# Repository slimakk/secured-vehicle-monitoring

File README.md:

# SECURED VEHICLE MONITORING USING OBDII AND LPWAN NETWORKS

This repository contains hardware design files and source code for bachelor thesis at FEEC BUT, which was sucessfully defended in 2023. The main goal behind the creation of this thesis was to create a device that would be capable of reporting important engine parameters to an external server for further processing.

[Link to a full thesis](https://www.vut.cz/studenti/zav-prace?zp_id=151037)
---------------------------------------------------------------------------
## Hardware specs
* MCU -- STM32 L431
* LPWAN module -- Quectel BG77, supports NB-IoT, LTE Cat M, GPS
* Power -- Synchronous Step-Down Converter by Texas Instruments
* Vehicle comms -- CAN Bus, K-Line, KWP2000
## Software
* OBD II support -- only mode 02
* Data transmission -- UDP, TCP, MQTT

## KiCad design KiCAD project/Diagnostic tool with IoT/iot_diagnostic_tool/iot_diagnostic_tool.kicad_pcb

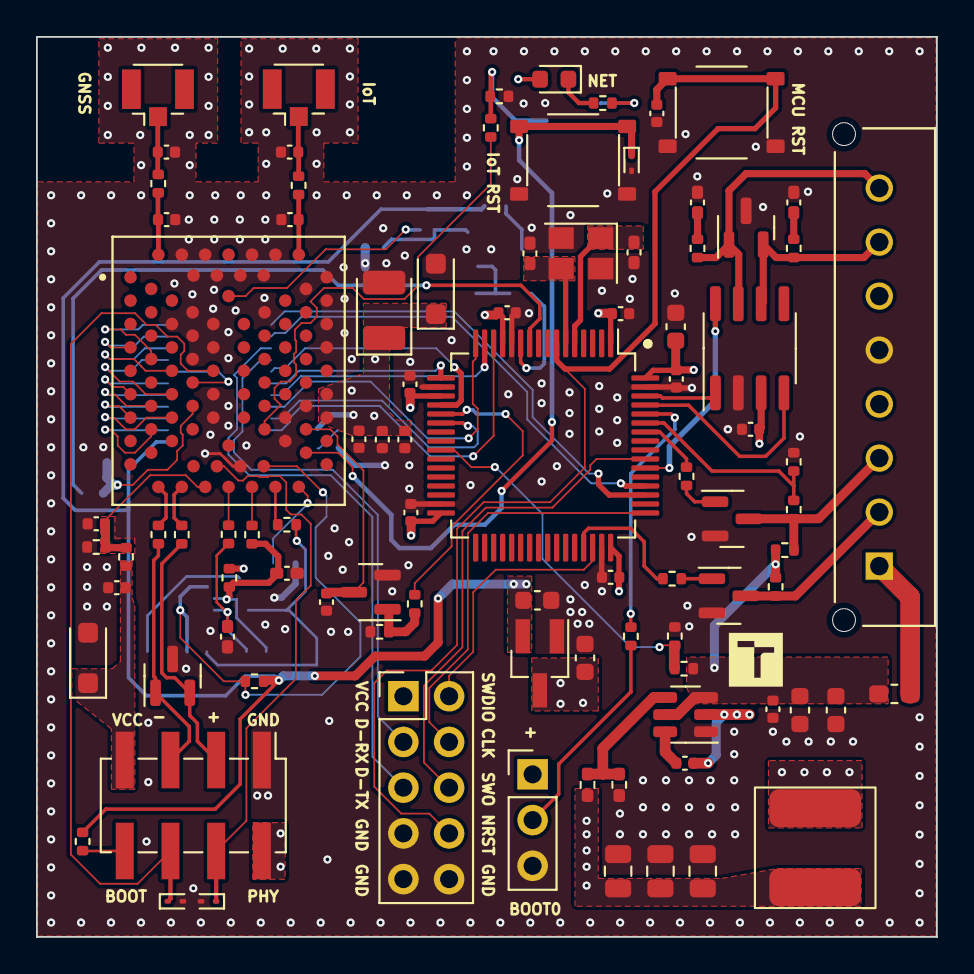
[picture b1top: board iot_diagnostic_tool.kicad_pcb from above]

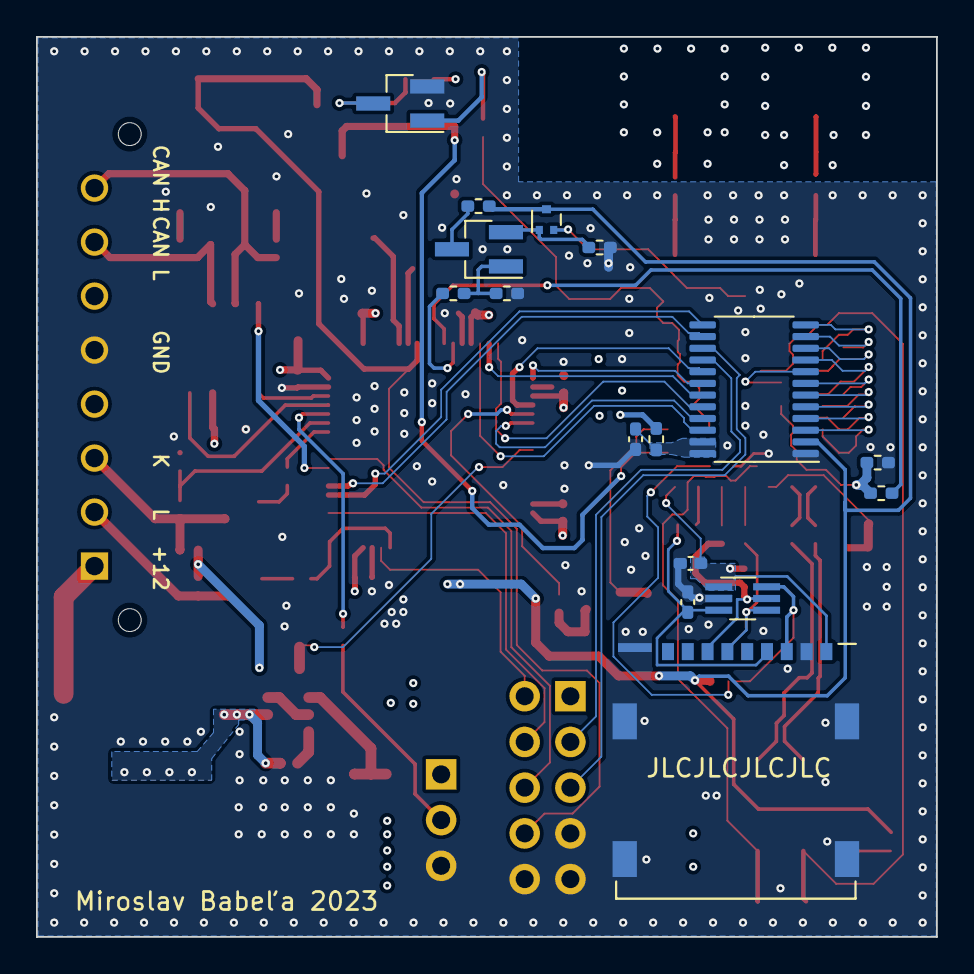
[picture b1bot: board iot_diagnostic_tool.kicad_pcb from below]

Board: 4 copper layers, 50.0 x 50.0 mm, 108 parts (16 on the bottom side), 88 nets.

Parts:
AE1: IoT_ANT; U.FL_Hirose_U.FL-R-SMT-1_Vertical
AE2: GNSS_ANT; U.FL_Hirose_U.FL-R-SMT-1_Vertical
C1: 4u7; C_0603_1608Metric
C2, C3, C4, C5, C6, C7, C8, C11, C14, C18, C23, C36: 100n; C_0402_1005Metric
C9, C10: 8p; C_0402_1005Metric_Pad0.74x0.62mm_HandSolder
C12, C13: 10u; C_0603_1608Metric
C15, C16, C17: 22u; C_0805_2012Metric
C19, C20: 560p; C_0402_1005Metric_Pad0.74x0.62mm_HandSolder
C21: 10p; C_0402_1005Metric
C22: 33p; C_0402_1005Metric
C24: 100u; CP_EIA-3528-21_Kemet-B
C25, C37: 10n; C_0402_1005Metric
C27, C32: 100n; C_0402_1005Metric_Pad0.74x0.62mm_HandSolder
C28, C29: 1u; C_0603_1608Metric
C33, C34, C35: 33p; C_0402_1005Metric_Pad0.74x0.62mm_HandSolder
C38, C39, C40, C41: NM; C_0402_1005Metric
D1: PESD2CAN; SOT-23
D2: LED; D_0603_1608Metric
D5: PESD5V0L5UY; SOT-363_SC-70-6_Handsoldering
D6, D11: TPSMF4L5.0A; D_SOD-123F
D7: PESD5V0X1BT,215; SOT-23
D8, D9, D10: ESD9L3.3; D_SOD-923
F1: 2A; Fuse_0603_1608Metric_Pad1.05x0.95mm_HandSolder
J2: USB; PinHeader_2x04_P2.54mm_Vertical_SMD
J3: 693023010811
J5: Debug; PinHeader_2x05_P2.54mm_Vertical
J6: BOOT; PinHeader_1x03_P2.54mm_Vertical
J7: OBD; MOLEX_436500827
L1: 3u3; VLS6045AF
Q1, Q2, Q4: BC817; SOT-23
Q3, Q5: BC817; SOT-23_Handsoldering
Q6: RUM001L02T2CL; SOT-723
R1, R34, R37: 10k; R_0402_1005Metric
R2: 33k2; R_0402_1005Metric_Pad0.72x0.64mm_HandSolder
R3, R40, R41, R44, R45: 10k; R_0402_1005Metric_Pad0.72x0.64mm_HandSolder
R4, R5: 100R; R_0402_1005Metric
R6, R8, R17: 2k2; R_0402_1005Metric
R7, R9: 510R; R_0402_1005Metric
R10, R12: 100k; R_0402_1005Metric
R11, R13: 27k; R_0402_1005Metric
R14, R18: 4k7; R_0402_1005Metric
R15, R19: 47k; R_0402_1005Metric
R16: 200k; R_0402_1005Metric_Pad0.72x0.64mm_HandSolder
R28, R29, R30, R35, R36, R38, R39: 0R; R_0402_1005Metric
R31: 51k; R_0402_1005Metric
R32: 15k; R_0402_1005Metric
R33: 20k; R_0402_1005Metric
R42, R43: 100k; R_0402_1005Metric_Pad0.72x0.64mm_HandSolder
SW1: RST; XKB_TS_1187A
SW3: IoT_RST; XKB_TS_1187A
U1: STM32L431RCTx; LQFP-64_10x10mm_P0.5mm
U2: TPS562201; SOT-23-6
U3: SN65HVD231; SOIC-8_3.9x4.9mm_P1.27mm
U4: BG77LA-64-SGNS; MODULE_BG77LA-64-SGNS
U6: AP2120N-1.8; SOT-23_Handsoldering
U8: NVT2010; TSSOP-24_4.4x7.8mm_P0.65mm
Y1: 16 MHz; Crystal_SMD_3225-4Pin_3.2x2.5mm

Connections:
+1V8: C29.1, Q6.3 (D), R31.1, R37.1, R40.1, U6.2 (VO), U8.2 (VREFA)
+3V3: C1.1, C2.1, C3.1, C4.1, C5.1, C6.1, C7.1, C15.1, C16.1, C17.1, C18.1, C21.1, C22.1, C23.1, C24.1, C28.1, D2.2 (A), D11.1 (K), J2.2, J5.1, J6.1, L1.2, R2.1, R16.1, U1.1 (VBAT), U1.13 (VDDA), U1.19 (VDD), U1.32 (VDD), U1.48 (VDD), U1.64 (VDD), U3.3 (VCC), U4.19 (VBAT), U4.20 (VBAT), U6.3 (VI)
+12V: F1.1, J7.1
/iot_module/antenna/ANT_G: AE2.1 (A), C41.1, R39.2
/iot_module/antenna/ANT_M: AE1.1 (A), C39.1, R38.2
/iot_module/sim/SIM_CL: C34.1, D5.4 (L3), J3.C3 (CLK), R29.2
/iot_module/sim/SIM_DAT: C35.1, D5.5 (L4), J3.C7 (I/O), R30.2, R32.2
/iot_module/sim/SIM_RES: C33.1, D5.3 (L2), J3.C2 (RST), R28.2
/power_supply/+12V_F: C11.1, C12.1, C13.1, F1.2, R7.1, R9.1, R12.1, U2.3 (VIN), U2.5 (EN)
/power_supply/BST: C14.2, U2.6 (VBST)
/power_supply/FB: R2.2, R3.1, U2.4 (VFB)
/power_supply/SW: C14.1, L1.1, U2.2 (SW)
ANT_GNSS: C40.1, R39.1, U4.32 (ANT_GNSS)
ANT_MAIN: C38.1, R38.1, U4.26 (ANT_MAIN)
AP_READY: R44.2, R45.1, U4.77 (AP_READY)
AP_READY_MCU: R44.1, U1.10 (PC2)
BAT_V: R12.2, R13.1, U1.25 (PC5)
BOOT0: R1.1, U1.60 (PH3)
CAN_H: D1.1 (A1), J7.8, R5.1, U3.7 (CANH)
CAN_L: D1.2 (A2), J7.7, R4.1, U3.6 (CANL)
CAN_RX: U1.61 (PB8), U3.4 (R)
CAN_S: U1.54 (PD2), U3.8 (Rs)
CAN_TX: U1.62 (PB9), U3.1 (D)
DBG_RX: J5.3, U8.16 (B7)
DBG_RXD: U4.61 (DBG_RXD), U8.9 (A7)
DBG_TX: J5.5, U8.15 (B8)
DBG_TXD: U4.60 (DBG_TXD), U8.10 (A8)
GND: C1.2, C2.2, C3.2, C4.2, C5.2, C6.2, C7.2, C8.2, C9.2, C10.2, C11.2, C12.2, C13.2, C15.2, C16.2, C17.2, C18.2, C19.2, C20.2, C21.2, C22.2, C23.2, C24.2, C25.2, C27.2, C28.2, C29.2, C32.2, C33.2, C34.2, C35.2, C36.1, C37.2, C38.2, C39.2, C40.2, C41.2, D1.3 (Com), D5.2 (VN), D6.2 (A), D7.3 (A), D8.2 (A), D9.2 (A), D10.2 (A), D11.2 (A), J2.1, J3.C5 (GND), J3.Z1 (GND1), J3.Z2 (GND1), J3.Z3 (GND1), J3.Z4 (GND1), J3.Z5 (GND1), J5.7, J5.9, J5.10, J6.3, J7.5, Q1.2 (E), Q2.2 (E), Q4.2 (E), Q5.2 (E), R3.2, R11.2, R13.2, R15.1, R19.1, R34.1, R42.2, R43.2, R45.2, SW1.1, SW3.2, U1.12 (VSSA), U1.18 (VSS), U1.31 (VSS), U1.47 (VSS), U1.63 (VSS), U2.1 (GND), U3.2 (GND), U4.22 (GND), U4.23 (GND), U4.24 (GND), U4.25 (GND), U4.27 (GND), U4.28 (GND), U4.30 (GND), U4.31 (GND), U4.43 (GND), U4.47 (GND), U4.52 (GND), U4.53 (GND), U4.54 (GND), U4.55 (GND), U4.56 (GND), U4.58 (GND), U4.65 (USIM_GND), U4.66 (GND), U4.73 (GND), U4.74 (GND), U4.75 (GND), U4.84 (GND), U4.85 (GND), U4.86 (GND), U4.88 (GND), U4.89 (GND), U6.1 (GND), U8.1 (GND), Y1.2, Y1.4
GNSS_RX: U1.52 (PC11), U8.14 (B9)
GNSS_RXD: U4.4 (GNSS_RXD), U8.11 (A9)
GNSS_TX: U1.51 (PC10), U8.13 (B10)
GNSS_TXD: U4.36 (GNSS_TXD), U8.12 (A10)
HSE_IN: C9.1, U1.5 (PH0), Y1.1
HSE_OUT: C10.1, U1.6 (PH1), Y1.3
ISO_K: J7.3, Q1.3 (C), R7.2, R10.1
ISO_L: J7.2, Q4.3 (C), R9.2
IoT_CTS: U1.14 (PA0), U8.22 (B1)
IoT_DTR: U1.22 (PA6), U8.21 (B2)
IoT_PWR: R14.1, U1.21 (PA5)
IoT_RI: U1.20 (PA4), U8.17 (B6)
IoT_RTS: U1.15 (PA1), U8.19 (B4)
IoT_RX: U1.17 (PA3), U8.18 (B5)
IoT_TX: U1.16 (PA2), U8.20 (B3)
K_Line_RX: R10.2, R11.1, U1.59 (PB7)
K_Line_TX: R6.2, U1.58 (PB6)
L_Line: R8.2, U1.45 (PA12)
MAIN_CTS: U4.39 (MAIN_CTS), U8.3 (A1)
MAIN_DTR: U4.62 (MAIN_DTR), U8.4 (A2)
MAIN_RI: U4.76 (MAIN_RI), U8.8 (A6)
MAIN_RTS: U4.38 (MAIN_RTS), U8.6 (A4)
MAIN_RXD: U4.6 (MAIN_RXD), U8.7 (A5)
MAIN_TXD: U4.7 (MAIN_TXD), U8.5 (A3)
NET_STATUS: R18.1, U4.79 (NET_STATUS)
NRST: C8.1, J5.8, SW1.2, U1.7 (NRST)
unnamed: C19.1, R4.2
unnamed: C20.1, R5.2
unnamed: D2.1 (K), R17.1
unnamed: J6.2, R1.2
unnamed: Q1.1 (B), R6.1
unnamed: Q2.1 (B), R14.2, R15.2
unnamed: Q3.1 (B), R41.2, R42.1
unnamed: Q3.3 (C), R40.2
unnamed: Q3.2 (E), Q6.1 (G), R43.1
unnamed: Q4.1 (B), R8.1
unnamed: Q5.1 (B), R18.2, R19.2
unnamed: Q5.3 (C), R17.2
unnamed: C27.1, R16.2, U8.23 (VREFB), U8.24 (EN)
PON_TRIG: Q6.2 (S), U4.72 (PON_TRIG)
PON_TRIG_MCU: R41.1, U1.11 (PC3)
PWRKEY: C25.1, Q2.3 (C), U4.46 (PWRKEY)
RESET_N: D10.1 (K), SW3.1, U4.45 (RESET_N)
SIM_CLK: R29.1, U4.13 (USIM_CLK)
SIM_DATA: R30.1, U4.14 (USIM_DATA)
SIM_DET: D5.6 (L5), J3.SW (DETECTION), R31.2, U4.44 (USIM_DET)
SIM_RST: R28.1, U4.15 (USIM_RST)
SIM_VDD: C32.1, D5.1 (L1), J3.C1 (VCC), R32.1, U4.16 (USIM_VDD)
SWCLK: J5.4, U1.49 (PA14)
SWDIO: J5.2, U1.46 (PA13)
SWO: J5.6, U1.55 (PB3)
USBPHY: D9.1 (K), J2.4, U4.42 (USBPHY_3P3)
USB_BOOT: D8.1 (K), J2.6, U4.87 (USB_BOOT)
USB_BOOT_VCC: J2.8, R37.2
USB_D+: R36.1, U4.11 (USB_DP)
USB_D+_5: D7.2 (K2), J2.3, R36.2
USB_D-: R35.1, U4.10 (USB_DM)
USB_D-_5: D7.1 (K1), J2.5, R35.2
USB_VBUS: C37.1, R33.1, R34.2, U4.12 (USB_VBUS)
USB_VBUS_5: C36.2, D6.1 (K), J2.7, R33.2

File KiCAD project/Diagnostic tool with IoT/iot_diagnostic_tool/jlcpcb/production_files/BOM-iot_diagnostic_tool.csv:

Comment,Designator,Footprint,LCSC
SN65HVD231,U3,SOIC-8_3.9x4.9mm_P1.27mm,C129257
16 MHz,Y1,Crystal_SMD_3225-4Pin_3.2x2.5mm,C13738
10n,"C25,C37",C_0402_1005Metric,C15195
10u,"C12,C13",C_0603_1608Metric,C1525
33p,C22,C_0402_1005Metric,C1562
1u,"C28,C29",C_0603_1608Metric,C15849
100u,C24,CP_EIA-3528-21_Kemet-B,C16133
0R,"R28,R29,R30,R35,R36,R38,R39",R_0402_1005Metric,C17168
4u7,C1,C_0603_1608Metric,C19666
BC817,"Q1,Q2,Q4",SOT-23,C2150
100R,"R4,R5",R_0402_1005Metric,C25076
510R,"R7,R9",R_0402_1005Metric,C25123
100k,"R10,R12",R_0402_1005Metric,C25741
10k,"R1,R34,R37",R_0402_1005Metric,C25744
15k,R32,R_0402_1005Metric,C25756
20k,R33,R_0402_1005Metric,C25765
27k,"R11,R13",R_0402_1005Metric,C25771
47k,"R15,R19",R_0402_1005Metric,C25792
51k,R31,R_0402_1005Metric,C25794
2k2,"R17,R6,R8",R_0402_1005Metric,C25879
4k7,"R14,R18",R_0402_1005Metric,C25900
PESD2CAN,D1,SOT-23,C284078
100n,"C11,C14,C18,C2,C23,C3,C36,C4,C5,C6,C7,C8",C_0402_1005Metric,C307331
RST,"SW1,SW3",XKB_TS_1187A,C318884
10p,C21,C_0402_1005Metric,C32949
22u,"C15,C16,C17",C_0805_2012Metric,C45783
IoT_ANT,"AE1,AE2",U.FL_Hirose_U.FL-R-SMT-1_Vertical,C88374
TPS562201,U2,SOT-23-6,C90061
STM32L431RCTx,U1,LQFP-64_10x10mm_P0.5mm,C92468
LED,D2,D_0603_1608Metric,

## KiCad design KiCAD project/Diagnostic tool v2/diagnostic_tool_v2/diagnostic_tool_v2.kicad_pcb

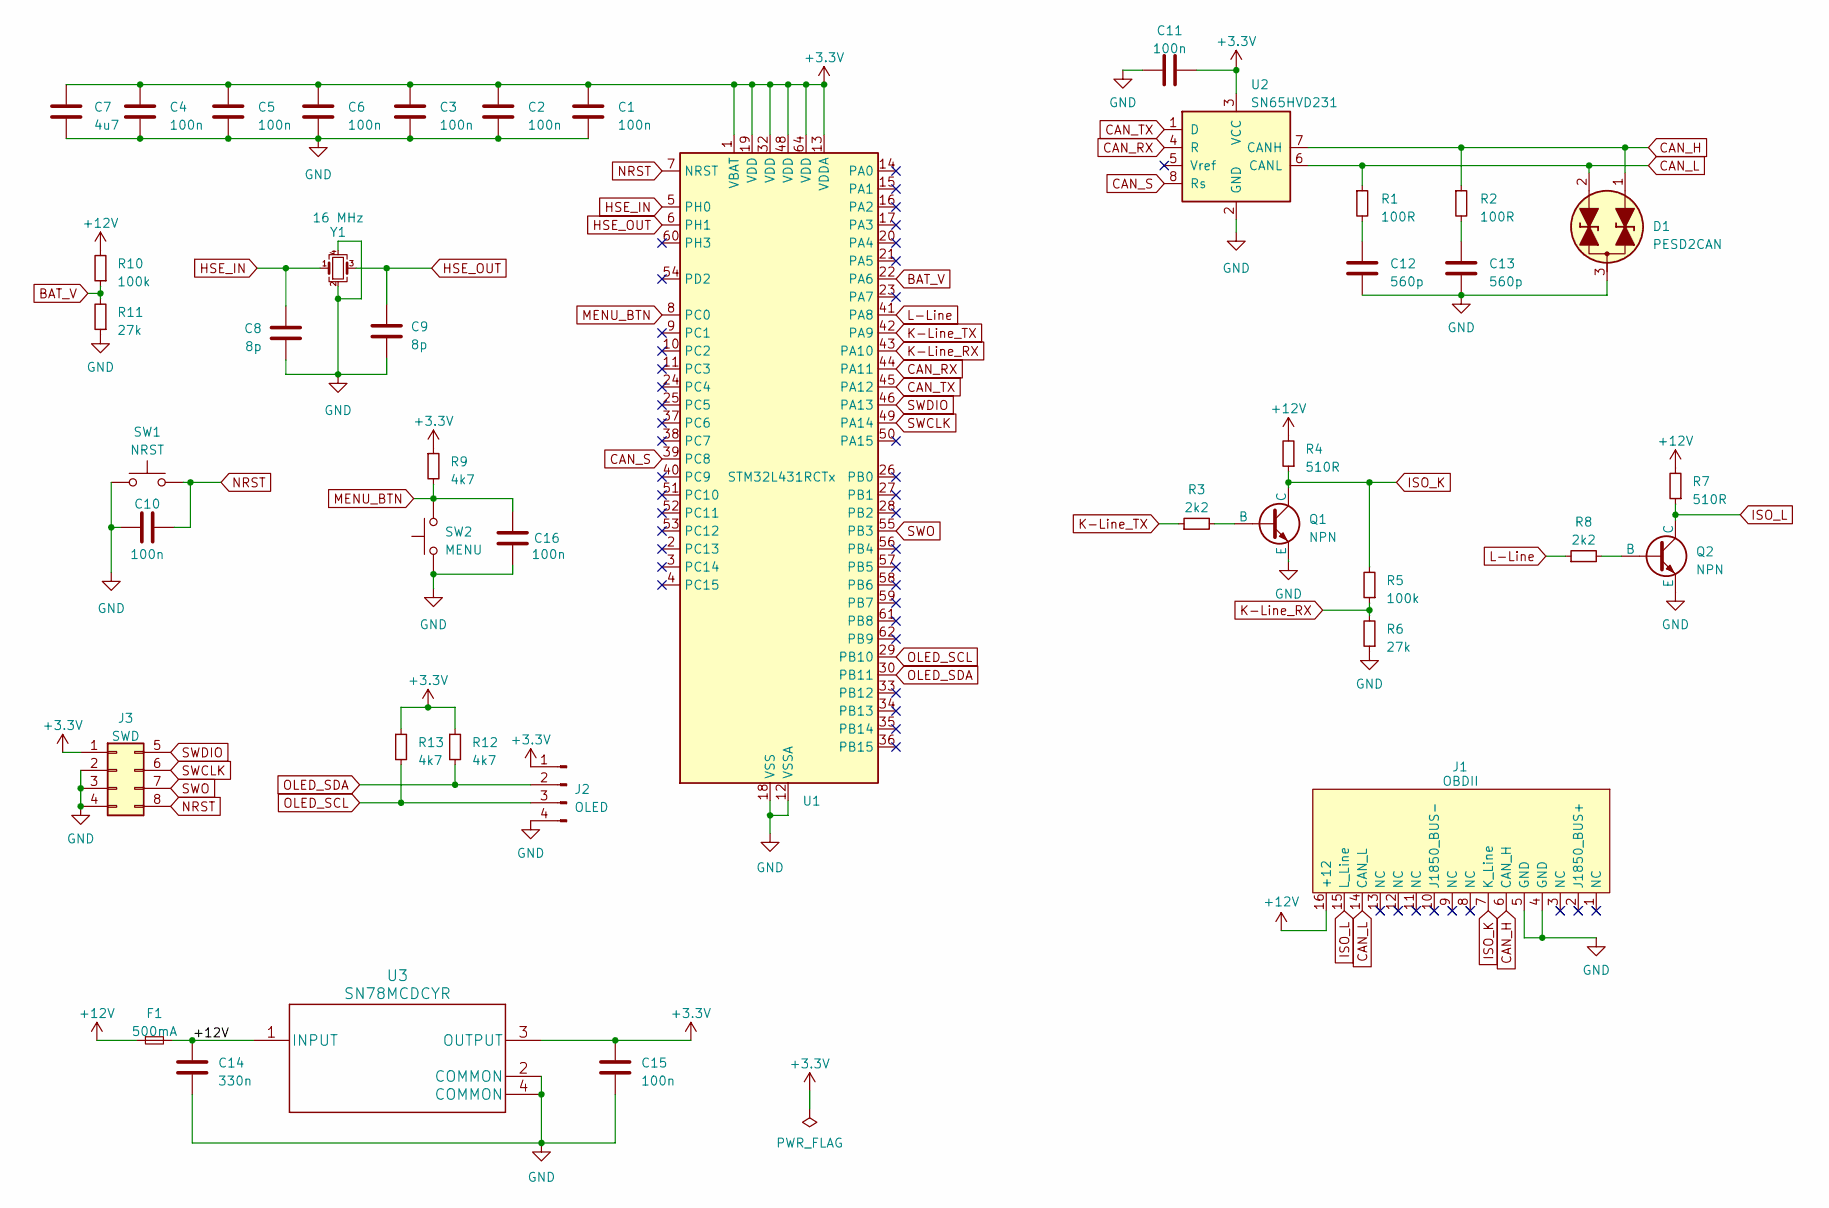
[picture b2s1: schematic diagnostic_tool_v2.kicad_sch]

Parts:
C1, C2, C3, C4, C5, C6, C10, C11, C15, C16: 100n; C_0402_1005Metric
C7: 4u7; C_0603_1608Metric
C8, C9: 8p; C_0402_1005Metric
C12, C13: 560p; C_0402_1005Metric
C14: 330n; C_0603_1608Metric
D1: PESD2CAN; SOT-23
F1: 500mA; Fuse_1206_3216Metric_Pad1.42x1.75mm_HandSolder
J1: OBDII; OBD
J2: OLED; PinHeader_1x04_P1.27mm_Vertical
J3: SWD; PinHeader_2x04_P1.27mm_Vertical
Q1, Q2: NPN; SOT-23
R1, R2: 100R; R_0402_1005Metric
R3, R8: 2k2; R_0402_1005Metric
R4, R7: 510R; R_0402_1005Metric
R5, R10: 100k; R_0402_1005Metric
R6, R11: 27k; R_0402_1005Metric
R9, R12, R13: 4k7; R_0402_1005Metric
SW1: NRST; XKB_TS_1187A
SW2: MENU; PinHeader_1x02_P1.27mm_Vertical
U1: STM32L431RCTx; LQFP-64_10x10mm_P0.5mm
U2: SN65HVD231; SOIC-8_3.9x4.9mm_P1.27mm
U3: SN78MCDCYR; SOT-223
Y1: 16 MHz; Crystal_SMD_TXC_7M-4Pin_3.2x2.5mm

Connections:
+3.3V: C1.1, C2.1, C3.1, C4.1, C5.1, C6.1, C7.1, C11.2, C15.1, J2.1, J3.1, R9.1, R12.1, R13.1, U1.1 (VBAT), U1.13 (VDDA), U1.19 (VDD), U1.32 (VDD), U1.48 (VDD), U1.64 (VDD), U2.3 (VCC), U3.3 (OUTPUT)
+12V: C14.1, F1.1, F1.2, J1.16 (+12), R4.2, R7.2, R10.2, U3.1 (INPUT)
BAT_V: R10.1, R11.2, U1.22 (PA6)
CAN_H: D1.1 (A1), J1.6 (CAN_H), R2.1, U2.7 (CANH)
CAN_L: D1.2 (A2), J1.14 (CAN_L), R1.1, U2.6 (CANL)
CAN_RX: U1.44 (PA11), U2.4 (R)
CAN_S: U1.39 (PC8), U2.8 (Rs)
CAN_TX: U1.45 (PA12), U2.1 (D)
GND: C1.2, C2.2, C3.2, C4.2, C5.2, C6.2, C7.2, C8.2, C9.2, C10.1, C11.1, C12.1, C13.1, C14.2, C15.2, C16.2, D1.3 (Com), J1.4 (GND), J1.5 (GND), J2.4, J3.2, J3.3, J3.4, Q1.3 (E), Q2.3 (E), R6.1, R11.1, SW1.1, SW2.1, U1.12 (VSSA), U1.18 (VSS), U1.31 (VSS), U1.47 (VSS), U1.63 (VSS), U2.2 (GND), U3.2 (COMMON), U3.4 (COMMON), Y1.2, Y1.4
HSE_IN: C8.1, U1.5 (PH0), Y1.1
HSE_OUT: C9.1, U1.6 (PH1), Y1.3
ISO_K: J1.7 (K_Line), Q1.1 (C), R4.1, R5.2
ISO_L: J1.15 (L_Line), Q2.1 (C), R7.1
K-Line_RX: R5.1, R6.2, U1.43 (PA10)
K-Line_TX: R3.1, U1.42 (PA9)
L-Line: R8.1, U1.41 (PA8)
MENU_BTN: C16.1, R9.2, SW2.2, U1.8 (PC0)
NRST: C10.2, J3.8, SW1.2, U1.7 (NRST)
unnamed: C12.2, R1.2
unnamed: C13.2, R2.2
unnamed: Q1.2 (B), R3.2
unnamed: Q2.2 (B), R8.2
OLED_SCL: J2.3, R13.2, U1.29 (PB10)
OLED_SDA: J2.2, R12.2, U1.30 (PB11)
SWCLK: J3.6, U1.49 (PA14)
SWDIO: J3.5, U1.46 (PA13)
SWO: J3.7, U1.55 (PB3)

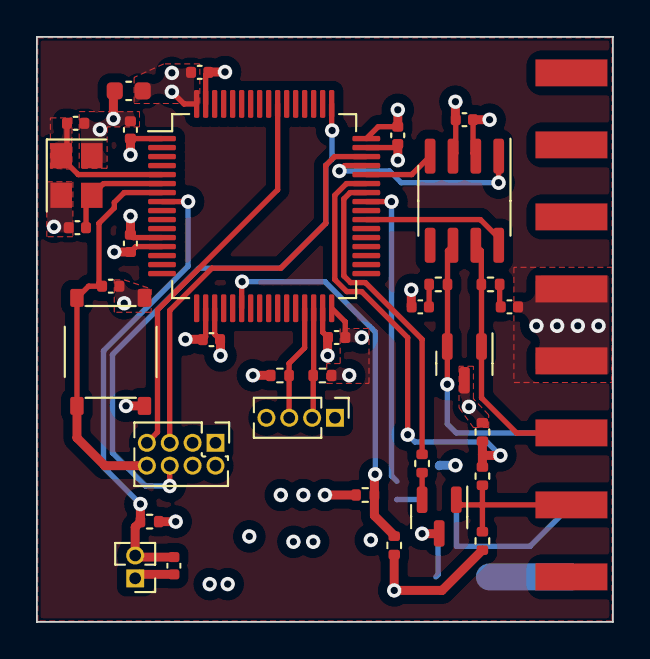
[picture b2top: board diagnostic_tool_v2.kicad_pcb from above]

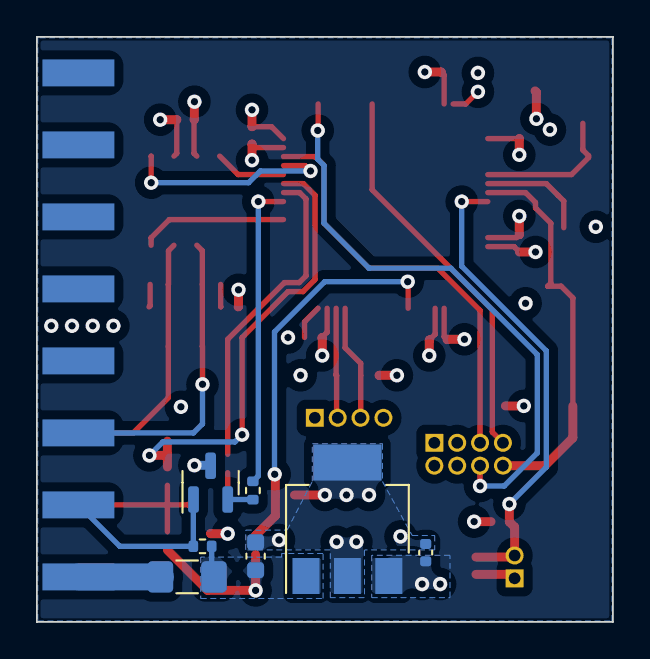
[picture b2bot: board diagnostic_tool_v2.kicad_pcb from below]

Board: 4 copper layers, 32.0 x 32.5 mm, 42 parts (7 on the bottom side), 27 nets.

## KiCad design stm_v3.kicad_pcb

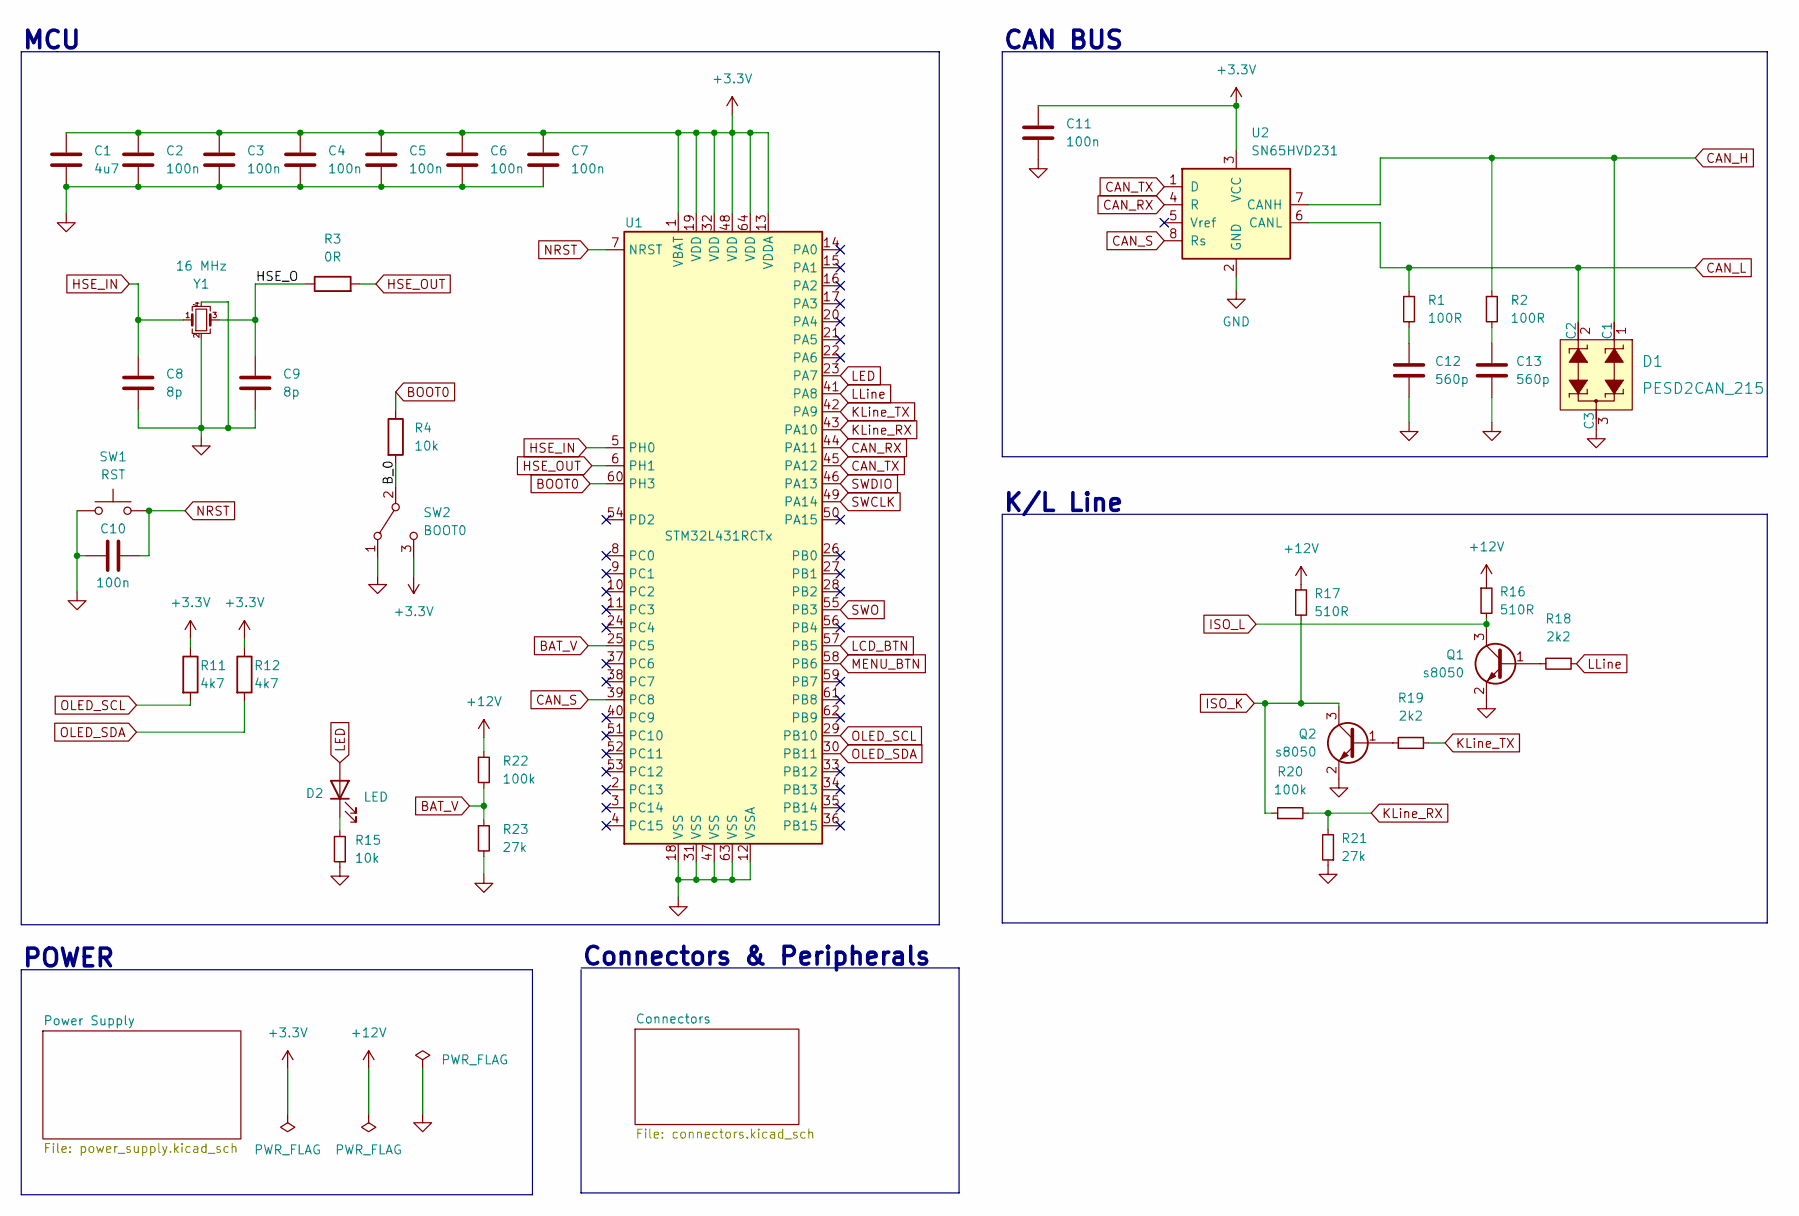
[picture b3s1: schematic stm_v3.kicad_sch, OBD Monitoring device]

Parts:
C1: 4u7; C_0603_1608Metric
C2, C3, C4, C5, C6, C7, C10, C11: 100n; C_0402_1005Metric
C8, C9: 8p; C_0402_1005Metric_Pad0.74x0.62mm_HandSolder
C12, C13: 560p; C_0402_1005Metric_Pad0.74x0.62mm_HandSolder
D1: PESD2CAN_215; SOT-23-3; MPN PESD2CAN,215; Digi-Key_PN 1727-3891-1-ND
D2: LED; LED_0603_1608Metric
Q1, Q2: s8050; SOT-23
R1, R2: 100R; R_0402_1005Metric
R3: 0R; R_0402_1005Metric
R4, R15: 10k; R_0402_1005Metric
R11, R12: 4k7; R_0402_1005Metric
R16, R17: 510R; R_0402_1005Metric
R18, R19: 2k2; R_0402_1005Metric
R20, R22: 100k; R_0402_1005Metric
R21, R23: 27k; R_0402_1005Metric
SW1: RST; XKB_TS_1187A
SW2: BOOT0; XKB_SS-3292S
U1: STM32L431RCTx; LQFP-64_10x10mm_P0.5mm
U2: SN65HVD231; SOIC-8_3.9x4.9mm_P1.27mm
Y1: 16 MHz; Crystal_SMD_3225-4Pin_3.2x2.5mm

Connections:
+3.3V: C1.1, C2.1, C3.1, C4.1, C5.1, C6.1, C7.1, C11.1, R11.1, R12.1, SW2.3 (C), U1.1 (VBAT), U1.13 (VDDA), U1.19 (VDD), U1.32 (VDD), U1.48 (VDD), U1.64 (VDD), U2.3 (VCC); also elsewhere on the board
+12V: R16.1, R17.1, R22.1; also elsewhere on the board
/B_0: R4.2, SW2.2 (B)
/HSE_O: C9.1, R3.1, Y1.3
BAT_V: R22.2, R23.1, U1.25 (PC5)
BOOT0: R4.1, U1.60 (PH3)
CAN_H: D1.1 (C1), R2.1, U2.7 (CANH); also elsewhere on the board
CAN_L: D1.2 (C2), R1.1, U2.6 (CANL); also elsewhere on the board
CAN_RX: U1.44 (PA11), U2.4 (R)
CAN_S: U1.39 (PC8), U2.8 (Rs)
CAN_TX: U1.45 (PA12), U2.1 (D)
GND: C1.2, C2.2, C3.2, C4.2, C5.2, C6.2, C7.2, C8.2, C9.2, C10.2, C11.2, C12.2, C13.2, D1.3 (C3), Q1.2 (E), Q2.2 (E), R15.1, R21.1, R23.2, SW1.1, SW2.1 (A), U1.12 (VSSA), U1.18 (VSS), U1.31 (VSS), U1.47 (VSS), U1.63 (VSS), U2.2 (GND), Y1.2, Y1.4; also elsewhere on the board
HSE_IN: C8.1, U1.5 (PH0), Y1.1
HSE_OUT: R3.2, U1.6 (PH1)
ISO_K: Q2.3 (C), R17.2, R20.1; also elsewhere on the board
ISO_L: Q1.3 (C), R16.2; also elsewhere on the board
KLine_RX: R20.2, R21.2, U1.43 (PA10)
KLine_TX: R19.1, U1.42 (PA9)
LCD_BTN: U1.57 (PB5); also elsewhere on the board
LED: D2.2 (A), U1.23 (PA7)
LLine: R18.1, U1.41 (PA8)
MENU_BTN: U1.58 (PB6); also elsewhere on the board
NRST: C10.1, SW1.2, U1.7 (NRST); also elsewhere on the board
unnamed: C12.1, R1.2
unnamed: C13.1, R2.2
unnamed: D2.1 (K), R15.2
unnamed: Q1.1 (B), R18.2
unnamed: Q2.1 (B), R19.2
OLED_SCL: R11.2, U1.29 (PB10); also elsewhere on the board
OLED_SDA: R12.2, U1.30 (PB11); also elsewhere on the board
SWCLK: U1.49 (PA14); also elsewhere on the board
SWDIO: U1.46 (PA13); also elsewhere on the board
SWO: U1.55 (PB3); also elsewhere on the board

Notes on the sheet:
Connectors & Peripherals
MCU
POWER
K/L Line
CAN BUS

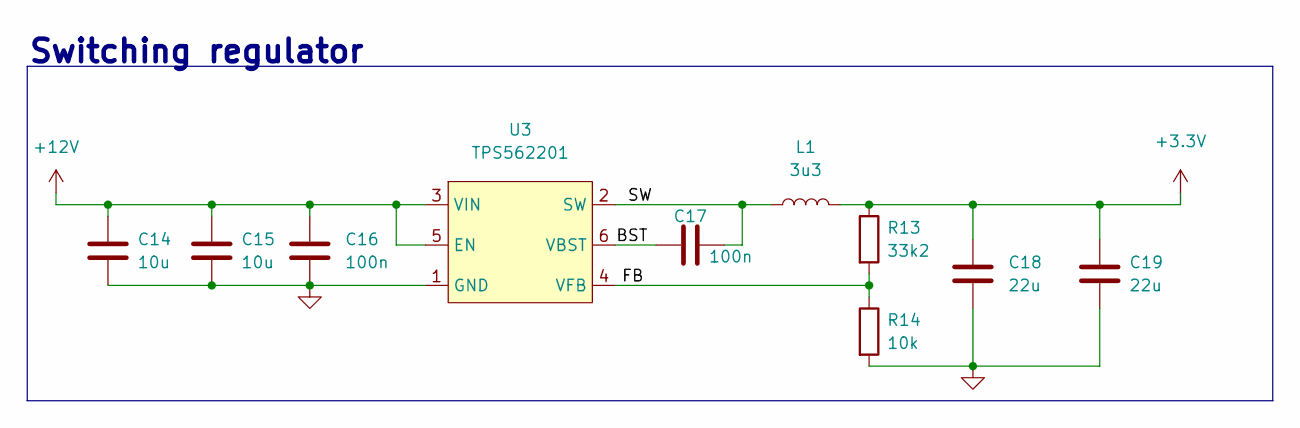
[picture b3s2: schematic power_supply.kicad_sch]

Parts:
C14, C15: 10u; C_0603_1608Metric
C16, C17: 100n; C_0402_1005Metric
C18, C19: 22u; C_1206_3216Metric
L1: 3u3; VLS6045AF
R13: 33k2; R_0402_1005Metric_Pad0.72x0.64mm_HandSolder
R14: 10k; R_0402_1005Metric_Pad0.72x0.64mm_HandSolder
U3: TPS562201; SOT-23-6

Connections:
+3.3V: C18.1, C19.1, L1.2, R13.1; also elsewhere on the board
+12V: C14.1, C15.1, C16.1, U3.3 (VIN), U3.5 (EN); also elsewhere on the board
/Power Supply/BST: C17.1, U3.6 (VBST)
/Power Supply/FB: R13.2, R14.1, U3.4 (VFB)
/Power Supply/SW: C17.2, L1.1, U3.2 (SW)
GND: C14.2, C15.2, C16.2, C18.2, C19.2, R14.2, U3.1 (GND); also elsewhere on the board

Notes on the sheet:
Switching regulator

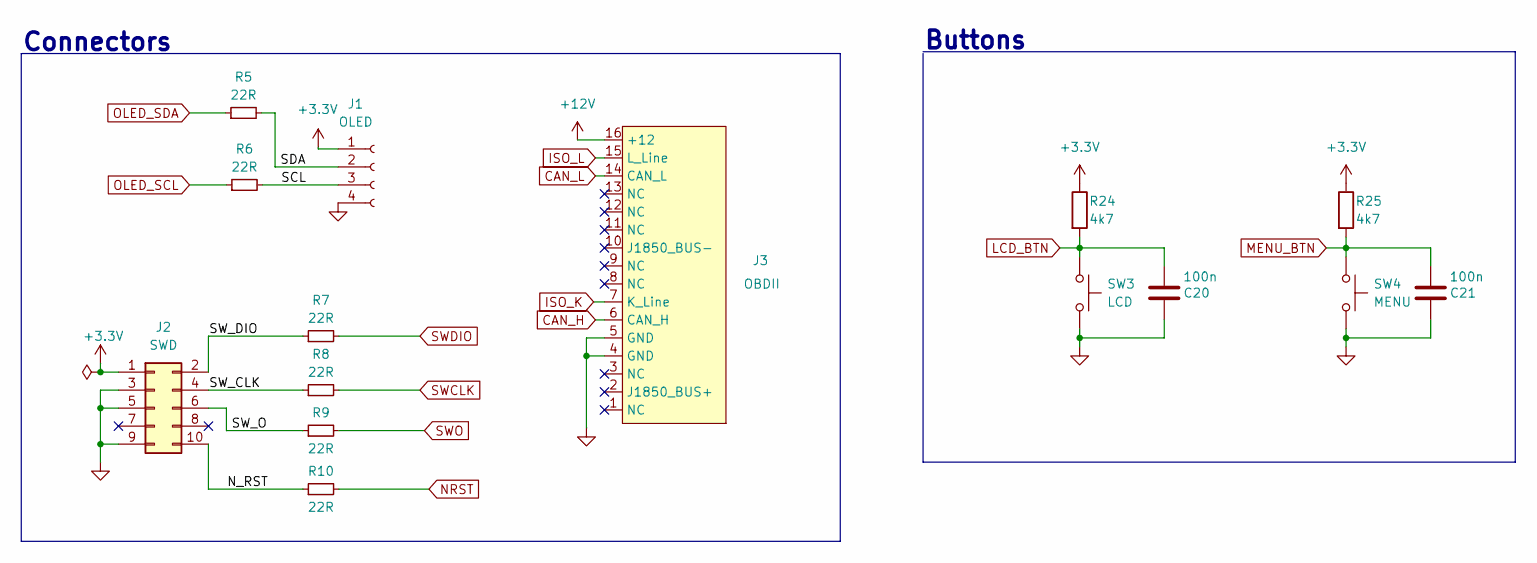
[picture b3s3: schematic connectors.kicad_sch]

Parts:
C20, C21: 100n; C_0402_1005Metric
J1: OLED; PinHeader_1x04_P2.54mm_Vertical
J2: SWD; PinHeader_2x05_P2.54mm_Vertical
J3: OBDII; OBD
R5, R6, R7, R8, R9, R10: 22R; R_0603_1608Metric
R24, R25: 4k7; R_0402_1005Metric
SW3: LCD; PinHeader_1x02_P1.27mm_Vertical
SW4: MENU; PinHeader_1x02_P1.27mm_Vertical

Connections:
+3.3V: J1.1, J2.1, R24.1, R25.1; also elsewhere on the board
+12V: J3.16 (+12); also elsewhere on the board
/Connectors/N_RST: J2.10, R10.1
/Connectors/SCL: J1.3, R6.2
/Connectors/SDA: J1.2, R5.2
/Connectors/SW_CLK: J2.4, R8.1
/Connectors/SW_DIO: J2.2, R7.1
/Connectors/SW_O: J2.6, R9.1
CAN_H: J3.6 (CAN_H); also elsewhere on the board
CAN_L: J3.14 (CAN_L); also elsewhere on the board
GND: C20.1, C21.1, J1.4, J2.3, J2.5, J2.9, J3.4 (GND), J3.5 (GND), SW3.2, SW4.2; also elsewhere on the board
ISO_K: J3.7 (K_Line); also elsewhere on the board
ISO_L: J3.15 (L_Line); also elsewhere on the board
LCD_BTN: C20.2, R24.2, SW3.1; also elsewhere on the board
MENU_BTN: C21.2, R25.2, SW4.1; also elsewhere on the board
NRST: R10.2; also elsewhere on the board
OLED_SCL: R6.1; also elsewhere on the board
OLED_SDA: R5.1; also elsewhere on the board
SWCLK: R8.2; also elsewhere on the board
SWDIO: R7.2; also elsewhere on the board
SWO: R9.2; also elsewhere on the board

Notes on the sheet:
Buttons
Connectors

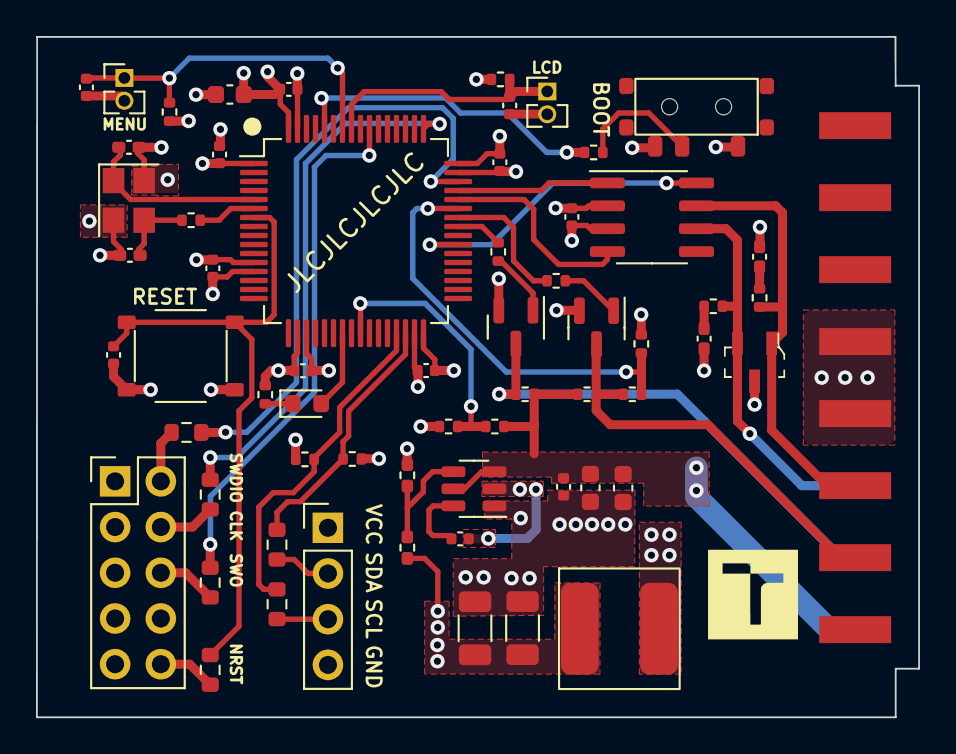
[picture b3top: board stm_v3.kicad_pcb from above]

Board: 4 copper layers, 49.0 x 37.8 mm, 62 parts (0 on the bottom side), 42 nets.

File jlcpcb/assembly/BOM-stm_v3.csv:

Comment,Designator,Footprint,LCSC
10k,"R15,R4",R_0402_1005Metric,C11616
SN65HVD231,U2,SOIC-8_3.9x4.9mm_P1.27mm,C129257
16 MHz,Y1,Crystal_SMD_3225-4Pin_3.2x2.5mm,C13738
100n,"C10,C11,C17,C2,C20,C21,C3,C4,C5,C6,C7",C_0402_1005Metric,C1525
0R,R3,R_0402_1005Metric,C17168
4u7,C1,C_0603_1608Metric,C19666
s8050,"Q1,Q2",SOT-23,C2146
22R,"R10,R5,R6,R7,R8,R9",R_0603_1608Metric,C23345
100R,"R1,R2",R_0402_1005Metric,C25076
510R,"R16,R17",R_0402_1005Metric,C25123
100k,"R20,R22",R_0402_1005Metric,C25741
27k,"R21,R23",R_0402_1005Metric,C25771
2k2,"R18,R19",R_0402_1005Metric,C25879
4k7,"R11,R12,R24,R25",R_0402_1005Metric,C25900
100n,C16,C_0402_1005Metric,C307331
RST,SW1,XKB_TS_1187A,C318884
BOOT0,SW2,XKB_SS-3292S,C397350
22u,"C18,C19",C_1206_3216Metric,C5672
LED,D2,LED_0603_1608Metric,C72038
PESD2CAN_215,D1,SOT-23-3,C75176
TPS562201,U3,SOT-23-6,C90061
STM32L431RCTx,U1,LQFP-64_10x10mm_P0.5mm,C92468
10u,"C14,C15",C_0603_1608Metric,C96446

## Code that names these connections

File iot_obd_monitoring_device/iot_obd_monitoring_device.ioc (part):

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Mcu.Name=STM32L431R(B-C)Tx
Mcu.Package=LQFP64
Mcu.UserName=STM32L431RCTx
PA0.GPIOParameters=GPIO_Label
PA0.GPIO_Label=IoT_CTS
PA0.Mode=CTS_RTS
PA0.Signal=USART2_CTS
PA1.GPIOParameters=GPIO_Label
PA1.GPIO_Label=IoT_RTS
PA1.Mode=CTS_RTS
PA1.Signal=USART2_RTS
PA12.GPIOParameters=GPIO_Label
PA12.GPIO_Label=L_Line
PA12.Signal=GPIO_Output
PA13\ (JTMS-SWDIO).GPIOParameters=GPIO_Label
PA13\ (JTMS-SWDIO).GPIO_Label=SWDIO
PA13\ (JTMS-SWDIO).Mode=Trace_Asynchronous_SW
PA13\ (JTMS-SWDIO).Signal=SYS_JTMS-SWDIO
PA14\ (JTCK-SWCLK).GPIOParameters=GPIO_Label
PA14\ (JTCK-SWCLK).GPIO_Label=SWCLK
PA14\ (JTCK-SWCLK).Mode=Trace_Asynchronous_SW
PA14\ (JTCK-SWCLK).Signal=SYS_JTCK-SWCLK
PA2.GPIOParameters=GPIO_PuPd,GPIO_Label
PA2.GPIO_Label=IoT_TX
PA2.GPIO_PuPd=GPIO_PULLUP
PA2.Mode=Asynchronous
PA2.Signal=USART2_TX
PA3.GPIOParameters=GPIO_Label
PA3.GPIO_Label=IoT_RX
PA3.Mode=Asynchronous
PA3.Signal=USART2_RX
PA4.GPIOParameters=GPIO_Label
PA4.GPIO_Label=IoT_RI
PA4.Signal=GPIO_Input
PA5.GPIOParameters=GPIO_Label
PA5.GPIO_Label=IoT_PWR
PA5.Signal=GPIO_Output
PA6.GPIOParameters=GPIO_Label
PA6.GPIO_Label=IoT_DTR
PA6.Signal=GPIO_Input
PB3\ (JTDO-TRACESWO).GPIOParameters=GPIO_Label
PB3\ (JTDO-TRACESWO).GPIO_Label=SWO
PB3\ (JTDO-TRACESWO).Mode=Trace_Asynchronous_SW
PB3\ (JTDO-TRACESWO).Signal=SYS_JTDO-SWO
PB6.GPIOParameters=GPIO_Label
PB6.GPIO_Label=K_Line_TX
PB6.Mode=Asynchronous
PB6.Signal=USART1_TX
PB7.GPIOParameters=GPIO_Label
PB7.GPIO_Label=K_Line_RX
PB7.Mode=Asynchronous
PB7.Signal=USART1_RX
PB8.Mode=CAN_Activate
PB8.Signal=CAN1_RX
PB9.Mode=CAN_Activate
PB9.Signal=CAN1_TX
PC2.GPIOParameters=GPIO_Label
PC2.GPIO_Label=AP_READY
PC2.Signal=GPIO_Output
PC3.GPIOParameters=GPIO_Label
PC3.GPIO_Label=PON_TRIG
PC3.Signal=GPIO_Output
PC5.GPIOParameters=GPIO_Label
PC5.GPIO_Label=BAT_V
PC5.Signal=ADCx_IN14
PD2.GPIOParameters=GPIO_Label
PD2.GPIO_Label=CAN_S
PD2.Signal=GPIO_Output
PH0-OSC_IN\ (PH0).GPIOParameters=GPIO_Label
PH0-OSC_IN\ (PH0).GPIO_Label=HSE_IN
PH0-OSC_IN\ (PH0).Mode=HSE-External-Oscillator
PH0-OSC_IN\ (PH0).Signal=RCC_OSC_IN
PH1-OSC_OUT\ (PH1).GPIOParameters=GPIO_Label
PH1-OSC_OUT\ (PH1).GPIO_Label=HSE_OUT
PH1-OSC_OUT\ (PH1).Mode=HSE-External-Oscillator
PH1-OSC_OUT\ (PH1).Signal=RCC_OSC_OUT
RCC.HSE_VALUE=16000000
RCC.SYSCLKFreq_VALUE=80000000
RCC.SYSCLKSource=RCC_SYSCLKSOURCE_PLLCLK
board=custom

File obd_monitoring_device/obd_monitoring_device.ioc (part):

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Mcu.Name=STM32L431R(B-C)Tx
Mcu.Package=LQFP64
Mcu.UserName=STM32L431RCTx
PA10.GPIOParameters=GPIO_Label
PA10.GPIO_Label=KLine_RX
PA10.Mode=Asynchronous
PA10.Signal=USART1_RX
PA11.GPIOParameters=GPIO_Label
PA11.GPIO_Label=CAN_RX
PA11.Mode=CAN_Activate
PA11.Signal=CAN1_RX
PA12.GPIOParameters=GPIO_Label
PA12.GPIO_Label=CAN_TX
PA12.Mode=CAN_Activate
PA12.Signal=CAN1_TX
PA13\ (JTMS-SWDIO).GPIOParameters=GPIO_Label
PA13\ (JTMS-SWDIO).GPIO_Label=SWDIO
PA13\ (JTMS-SWDIO).Mode=Trace_Asynchronous_SW
PA13\ (JTMS-SWDIO).Signal=SYS_JTMS-SWDIO
PA14\ (JTCK-SWCLK).GPIOParameters=GPIO_Label
PA14\ (JTCK-SWCLK).GPIO_Label=SWCLK
PA14\ (JTCK-SWCLK).Mode=Trace_Asynchronous_SW
PA14\ (JTCK-SWCLK).Signal=SYS_JTCK-SWCLK
PA8.GPIOParameters=GPIO_Label
PA8.GPIO_Label=LLine
PA8.Signal=GPIO_Output
PA9.GPIOParameters=GPIO_Label
PA9.GPIO_Label=KLine_TX
PA9.Mode=Asynchronous
PA9.Signal=USART1_TX
PB10.GPIOParameters=GPIO_Label
PB10.GPIO_Label=OLED_SCL
PB10.Mode=I2C
PB10.Signal=I2C2_SCL
PB11.GPIOParameters=GPIO_Label
PB11.GPIO_Label=OLED_SDA
PB11.Mode=I2C
PB11.Signal=I2C2_SDA
PB3\ (JTDO-TRACESWO).GPIOParameters=GPIO_Label
PB3\ (JTDO-TRACESWO).GPIO_Label=SWO
PB3\ (JTDO-TRACESWO).Mode=Trace_Asynchronous_SW
PB3\ (JTDO-TRACESWO).Signal=SYS_JTDO-SWO
PB6.GPIOParameters=GPIO_Label
PB6.GPIO_Label=MENU_BTN
PB6.Signal=GPXTI6
PC5.GPIOParameters=GPIO_Label
PC5.GPIO_Label=BAT_V
PC5.Signal=ADCx_IN14
PC8.GPIOParameters=GPIO_PuPd,GPIO_Label
PC8.GPIO_Label=CAN_S
PC8.GPIO_PuPd=GPIO_PULLDOWN
PC8.Signal=GPIO_Output
PH0-OSC_IN\ (PH0).GPIOParameters=GPIO_Label
PH0-OSC_IN\ (PH0).GPIO_Label=HSE_IN
PH0-OSC_IN\ (PH0).Mode=HSE-External-Oscillator
PH0-OSC_IN\ (PH0).Signal=RCC_OSC_IN
PH1-OSC_OUT\ (PH1).GPIOParameters=GPIO_Label
PH1-OSC_OUT\ (PH1).GPIO_Label=HSE_OUT
PH1-OSC_OUT\ (PH1).Mode=HSE-External-Oscillator
PH1-OSC_OUT\ (PH1).Signal=RCC_OSC_OUT
RCC.HSE_VALUE=16000000
RCC.SYSCLKFreq_VALUE=80000000
RCC.SYSCLKSource=RCC_SYSCLKSOURCE_PLLCLK
board=custom

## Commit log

2022-10-25 Board v2 - reduced size
2022-10-27 Further board size reduction
2022-11-01 Final board version
2022-11-07 CAN Bus communication implemented
2022-11-24 24/11/22 update
2022-11-28 Update 28/11/22 CAN BUS - implemented, K Line - WIP, OLED implemented
2023-01-21 KLine update 21/01/23
2023-01-25 KLine update 25/01/23 - added watchdog
2023-01-25 Repo cleanup
2023-01-25 Repo cleanup - 2.0
2023-01-26 Checksum & Watchdog update 26/01/23
2023-01-29 Case update 29/01/23
2023-02-02 Case update 02/02/23
2023-02-05 Case update 05/02/23
2023-02-08 Update 08/02/23 - CAN Bus fixed, Button WIP
2023-02-09 Update 09/02/23 - Button update
2023-02-14 Update 14/02/23 - fixed KWP2000 & button debounce
2023-02-15 Update 15/02/23 - OBD2_Init needs improvement
2023-02-15 Update 2 15/02/23 - OBD2_Init refined
2023-02-18 Update 18/02/23 - added monitoring for battery voltage
2023-02-26 Update 27/02/23 - new schematic
2023-03-03 Update 03/03/23 - new schematic done
2023-03-06 Update 06/03/23 - new board layout WIP 70%
2023-03-07 Update 07/03/23 - board layout done
2023-03-13 Update 13/03/23 - Board layout fixes
2023-03-17 Update 17/03/23 - final board update, generated files for manufacturing
2023-04-01 Update 02/04/23 - BG77 driver WIP
2023-04-03 Update 03/04/23 - finished base AT comms, MQTT implementation started
2023-04-04 Update 04/04/23 - mqtt base
2023-04-05 Update 05/04/23 - added mqtt connect & disconnect
2023-04-24 Update 24/04/23 - send_commnand now uses idle detection to dertmine the length of response
2023-04-24 Update 2 24/04/23 - send_command bug fix
2023-04-26 Update 26/04/23 - added mqtt publish, first version of locations acquisition
2023-04-26 Update 2 26/04/23 - finished gps location parser
2023-04-26 Update 27/04/23 - set PSM added
2023-04-29 Update 29/04/23 - repaired mqtt_connect & send_command, added comments in the driver
2023-05-01 Update 01/05/23 - added data acquisition functions for MQTT transmission
2023-05-05 Update 05/05/23 - changed approach for response reception
2023-05-05 Update 06/05/23 - added STEP file of the iot board
2023-05-07 Update 07/05/23 - new step file for board
2023-05-08 Update 08/05/23 - new case design
2023-05-13 Update 13/05/13 - BG77 driver bug fix
2023-05-13 Update 14/05/23 - obd functionality bug fix
2023-06-26 Update 26/06/23 - Thesis release
